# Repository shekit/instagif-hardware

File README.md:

# Instagif Camera

This repo contains the STL files and eagle files for building the Instagif Camera. You can find the code here: https://github.com/shekit/instagif

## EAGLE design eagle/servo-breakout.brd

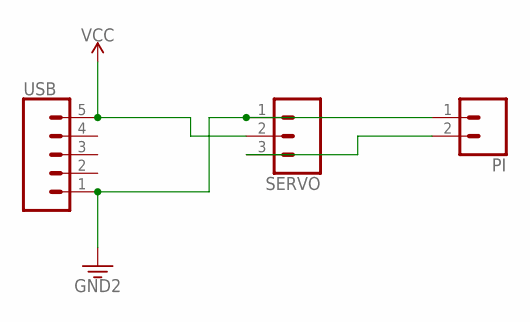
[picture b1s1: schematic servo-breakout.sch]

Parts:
PI: CONN_021X02_NO_SILK; 1X02_NO_SILK
SERVO: CONN_031X03_NO_SILK; 1X03_NO_SILK
USB: CONN_05NO_SILK; 1X05_NO_SILK

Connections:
3.3V: PI.1, SERVO.1, USB.1
unnamed: PI.2, SERVO.3
VCC: SERVO.2, USB.5

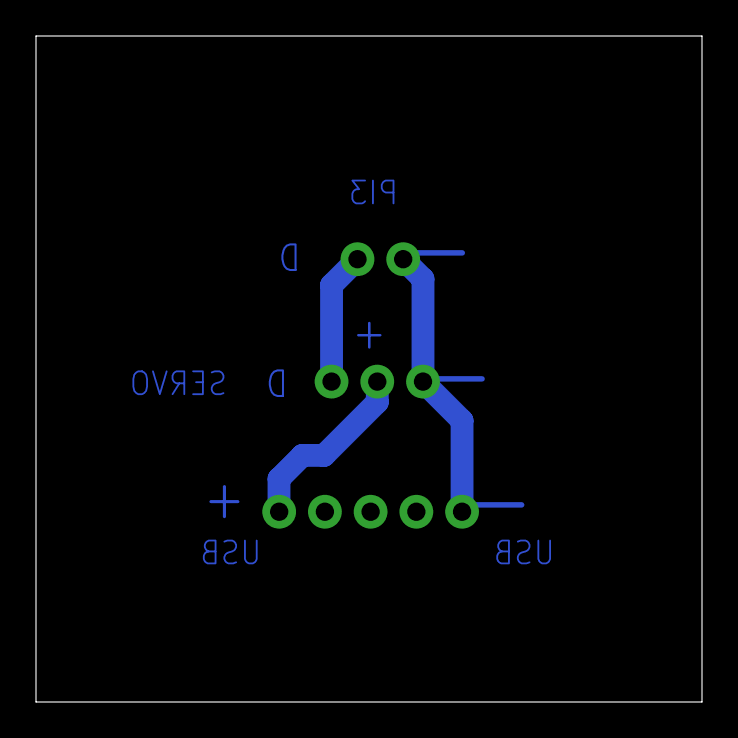
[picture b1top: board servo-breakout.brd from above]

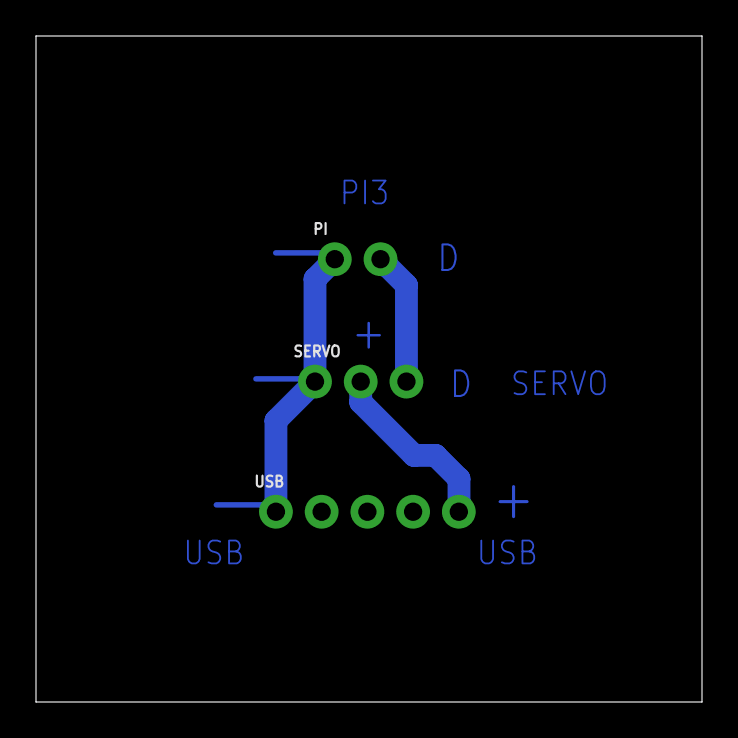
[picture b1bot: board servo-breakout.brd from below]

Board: 2 copper layers, 37.0 x 37.0 mm, 3 parts (3 on the bottom side), 3 nets.

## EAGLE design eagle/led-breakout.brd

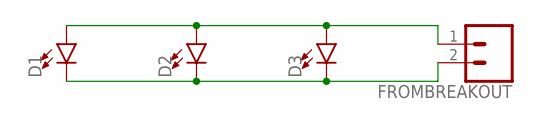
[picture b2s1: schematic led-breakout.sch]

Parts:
D1, D2, D3: LED3MM; LED_3MM
FROMBREAKOUT: CONN_021X02_NO_SILK; 1X02_NO_SILK

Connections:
unnamed: D1.A, D2.A, D3.A, FROMBREAKOUT.1
unnamed: D1.K (C), D2.K (C), D3.K (C), FROMBREAKOUT.2

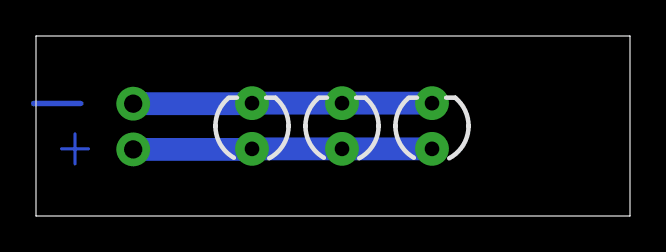
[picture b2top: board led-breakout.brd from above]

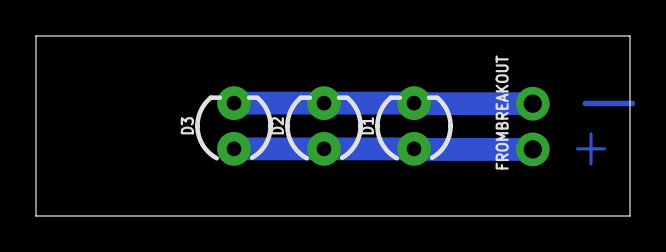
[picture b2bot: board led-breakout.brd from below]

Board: 2 copper layers, 33.0 x 10.0 mm, 4 parts (4 on the bottom side), 2 nets.

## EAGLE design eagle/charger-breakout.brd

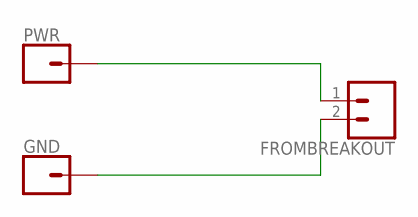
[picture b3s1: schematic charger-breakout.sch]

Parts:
FROMBREAKOUT: CONN_021X02_NO_SILK; 1X02_NO_SILK
GND: CONN_01SNAP-FEMALE; SNAP-FEMALE
PWR: CONN_01SNAP-FEMALE; SNAP-FEMALE

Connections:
unnamed: FROMBREAKOUT.1, PWR.1
unnamed: FROMBREAKOUT.2, GND.1

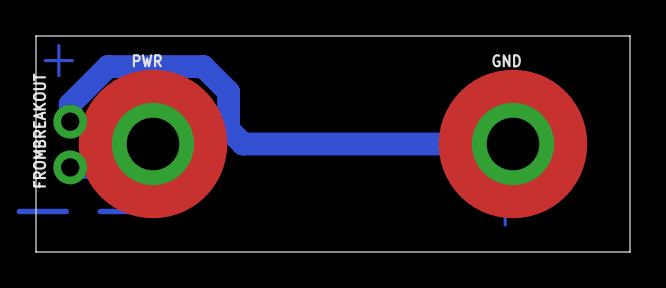
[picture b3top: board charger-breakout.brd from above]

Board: 2 copper layers, 33.0 x 12.0 mm, 3 parts (0 on the bottom side), 2 nets.

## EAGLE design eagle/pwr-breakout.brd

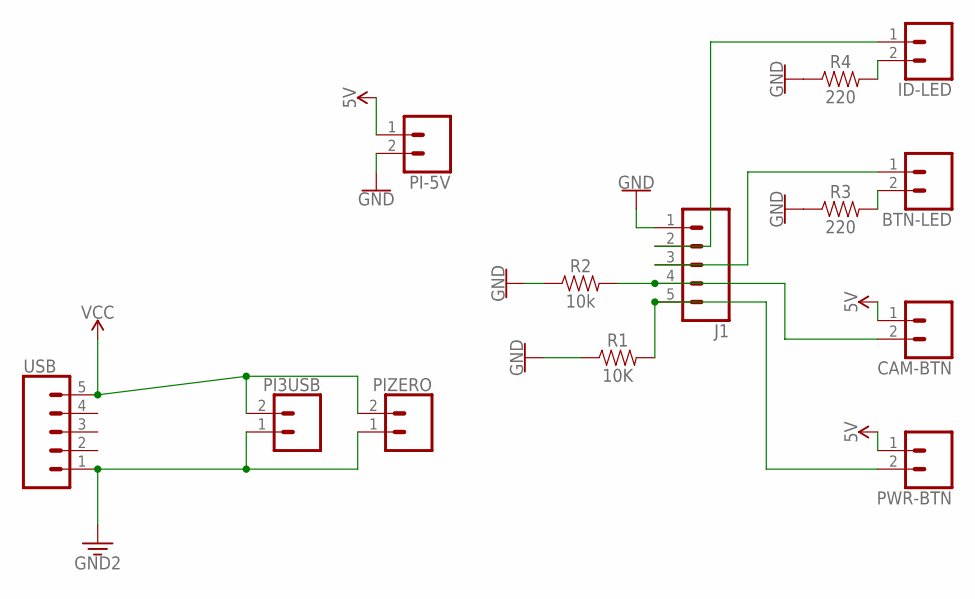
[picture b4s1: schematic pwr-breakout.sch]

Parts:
BTN-LED: CONN_021X02_NO_SILK; 1X02_NO_SILK
CAM-BTN: CONN_021X02_NO_SILK; 1X02_NO_SILK
ID-LED: CONN_021X02_NO_SILK; 1X02_NO_SILK
J1: CONN_05NO_SILK; 1X05_NO_SILK
PI3USB: CONN_021X02_NO_SILK; 1X02_NO_SILK
PI-5V: CONN_021X02_NO_SILK; 1X02_NO_SILK
PIZERO: CONN_021X02_NO_SILK; 1X02_NO_SILK
PWR-BTN: CONN_021X02_NO_SILK; 1X02_NO_SILK
R1: 10K; AXIAL-0.3
R2: 10k; AXIAL-0.3
R3, R4: 220; AXIAL-0.3
USB: CONN_05NO_SILK; 1X05_NO_SILK

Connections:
3.3V: PI3USB.1, PIZERO.1, USB.1
5V: CAM-BTN.1, PI-5V.1, PWR-BTN.1
GND: J1.1, PI-5V.2, R1.P$1 (1), R2.P$1 (1), R3.P$1 (1), R4.P$1 (1)
unnamed: J1.5, PWR-BTN.2, R1.P$2 (2)
unnamed: CAM-BTN.2, J1.4, R2.P$2 (2)
unnamed: ID-LED.2, R4.P$2 (2)
unnamed: BTN-LED.2, R3.P$2 (2)
unnamed: BTN-LED.1, J1.3
unnamed: ID-LED.1, J1.2
VCC: PI3USB.2, PIZERO.2, USB.5

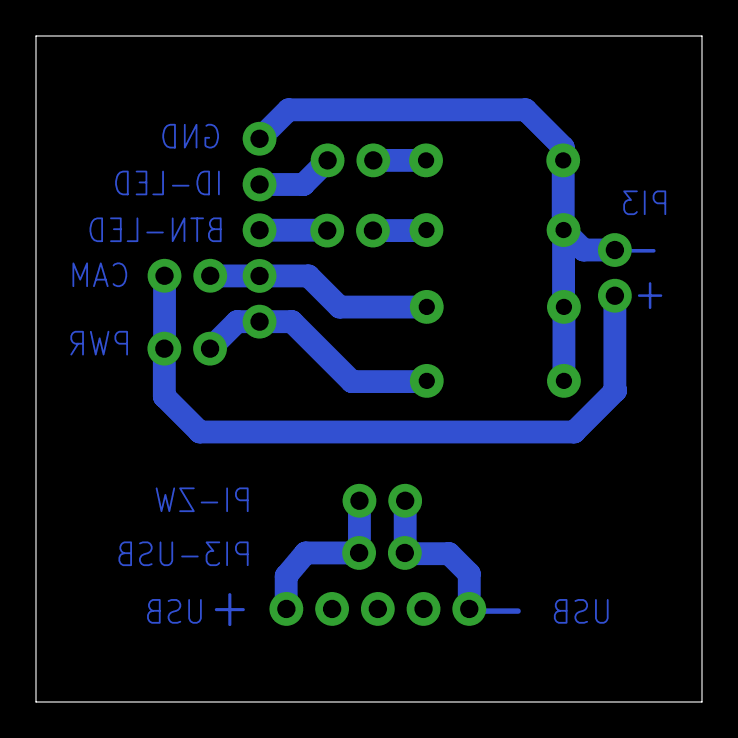
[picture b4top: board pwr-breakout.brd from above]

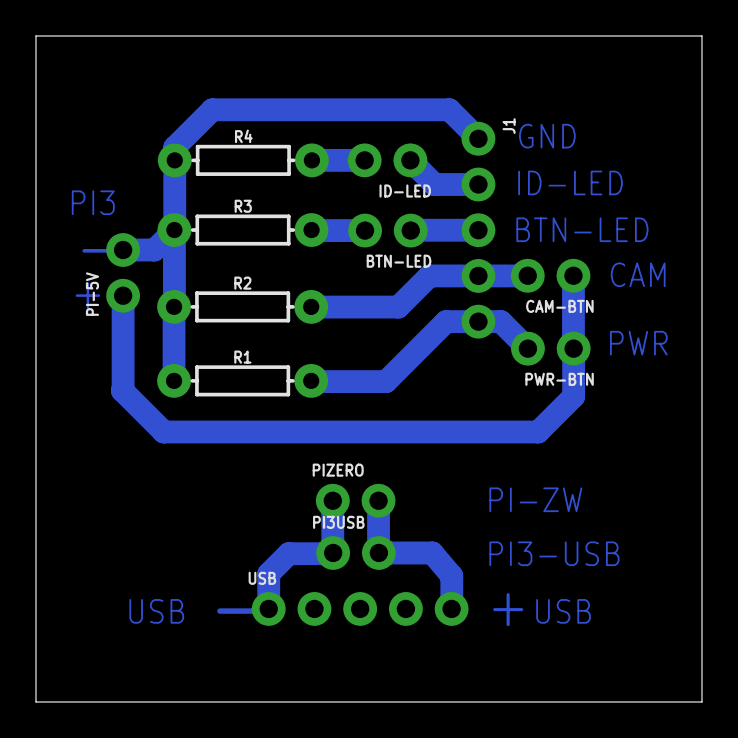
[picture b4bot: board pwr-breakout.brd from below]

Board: 2 copper layers, 37.0 x 37.0 mm, 13 parts (13 on the bottom side), 10 nets.

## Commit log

2017-08-26 all stl and eagle files

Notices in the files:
parts and their libraries:
SparkFun-Connectors: Licensing: Creative Commons ShareAlike 4.0 International - https://creativecommons.org/licenses/by-sa/4.0
